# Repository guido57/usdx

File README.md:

This software is derived from https://github.com/threeme3/usdx but it has been completely rewritten for ESP32-S3 N16R8 Devkit C1.

Its hardware is here https://hackaday.io/project/205224-esp32-hf-qrp-ft8-transceiver

# ESP32 SDR Receiver / FT8 Transceiver

This project implements a full **IQ SDR receiver** and **FT8 transceiver** on an ESP32 using external RF front-end circuitry. It includes DSP processing, **FT8 embedded coding and decoding**, audio output via I2S, network audio streaming, and automatic antenna band filtering.  

---

## Features

- True IQ SDR processing: **LSB/USB/AM/CW demodulation**
- High-quality ADC interface: **PCM1808**
- CIC decimation and DC removal
- IQ amplitude/phase calibration
- Selectable audio filters and **AGC**
- Volume control and RIT support
- **Network audio streaming** (websocket) over Wi-Fi or Ethernet
- **Web Server** for remote operations over Wi-Fi or Ethernet
- Automatic **antenna filter selection** via MCP23017 GPIO
- **FT8 TX and RX support** with frequency optimization
- **FT8 embedded coding and decoding** using my library https://github.com/guido57/ESP32_ft8_lib

---

## Architecture Overview

### 1️⃣ RF Front-End
- Tayloe / QSD detector for I/Q extraction
- Connected to **PCM1808 ADC** via I2S
- Optional analog pre-filtering per HF band

### 2️⃣ DSP / Demodulator Pipeline
PCM1808 ADC → CIC Decimator → DC Removal → IQ Calibration → Demodulator → Audio Filter → AGC → Volume → I2S / Wi-Fi

- **CIC Decimation:** 32 kHz → 8 kHz audio
- **IQ Calibration:** corrects phase and amplitude imbalance
- **Demodulator:** supports LSB, USB, AM, CW
- **Audio Filter:** selectable bandwidth for each mode
- **AGC:** peak limiting, attack/release control
- **Audio Output:** I2S DAC (MAX98357) or Wi-Fi streaming

### 3️⃣ RF Control

- **SI5351 driver** for local oscillator generation
- UI-controlled frequency, mode, and filter selection
- Automatic antenna filter switching via MCP23017
- **Filter selection rules:**
  - `< 4 MHz` → 1.8 / 3.5 MHz
  - `< 10 MHz` → 5 / 7 MHz
  - `< 30 MHz` → 14 / 21 / 28 MHz
  - `> 30 MHz` → bypass all

### 4️⃣ FT8 Subsystem

- Integrated **FT8 TX engine**
- Frequency optimization to avoid interferences
- For FT8 decoding, it continuosly streams audio to an external server where a python program:
  - receives audio
  - every 15 seconds runs a command line FT8 decoder (the same used by WSJT-X) to obtain the decoded messages
  - sends back decoded messages to the ESP32

### 5️⃣ Main Loop Execution

```text
loop():
 ├── ui_loop()                (UI interaction)
 ├── processAudioPCM1808()    (DSP pipeline)
 ├── SI5351 update if needed
 ├── antenna filter update
 ├── TX bias control
 └── periodic FT8 frequency optimization
```

### 6️⃣ Hardware Requirements

- ESP32 (any ESP32 variant with enough flash should work). I used ESP32-S3 N16R8 i.e. 16MB Flash, 8MB PSRAM
- PCM1808 ADC
- MAX98357 DAC (I2S audio)
- SI5351 frequency synthesizer
- MCP23017 for antenna relay switching
- Tayloe / QSD or other IQ front-end
- W5500 (optional) for Ethernet

### 7️⃣ Performance Notes

- Designed for efficient CPU usage on ESP32
- DSP pipeline supports real-time audio at 8 kHz
- Wi-Fi streaming allows network SDR operation
- Built-in calibration tools for IQ imbalance and clipping detection

### 8️⃣ ESP32-N16R8 memory partitioning
I adopted a custom partitioning as you can see in my  mypartitions.csv

```text
 Name,   Type, SubType, Offset,   Size, Flags
nvs,      data, nvs,      0x9000,   0x5000,
otadata,  data, ota,      0xe000,   0x2000,
app0,     app,  ota_0,    0x10000,  0x300000,   
app1,     app,  ota_1,    0x310000, 0x300000,   
logs,     data, spiffs,   0x610000, 0x200000,   
spiffs,   data, spiffs,   0x810000, 0x200000,   
coredump, data, coredump, 0xA10000, 0x20000,
```

I halved "data" into "logs" and "spiffs", both with a length of 0x200000 bytes:
- logs is read/written by the program (see qsostats.cpp) to persist QSO scoring but **it is not overwritten when I run 'pio run --target uploadfs'**
- spiffs contains all the files for the web server (index.html, app.js and so on), it is written with all the files contained in /data using 'pio run --target uploadfs' and it is read (only) by the program   

## Web User Interface

- answer a CQ double clicking a row
- follow the evolution of your or other QSOs 
- make a CQ or any other manual FT8 message
- set or disable the automatic frequency offset
- change the FT8 band (160, 80, 60, 40, 30, 20, 15, 10 meters)

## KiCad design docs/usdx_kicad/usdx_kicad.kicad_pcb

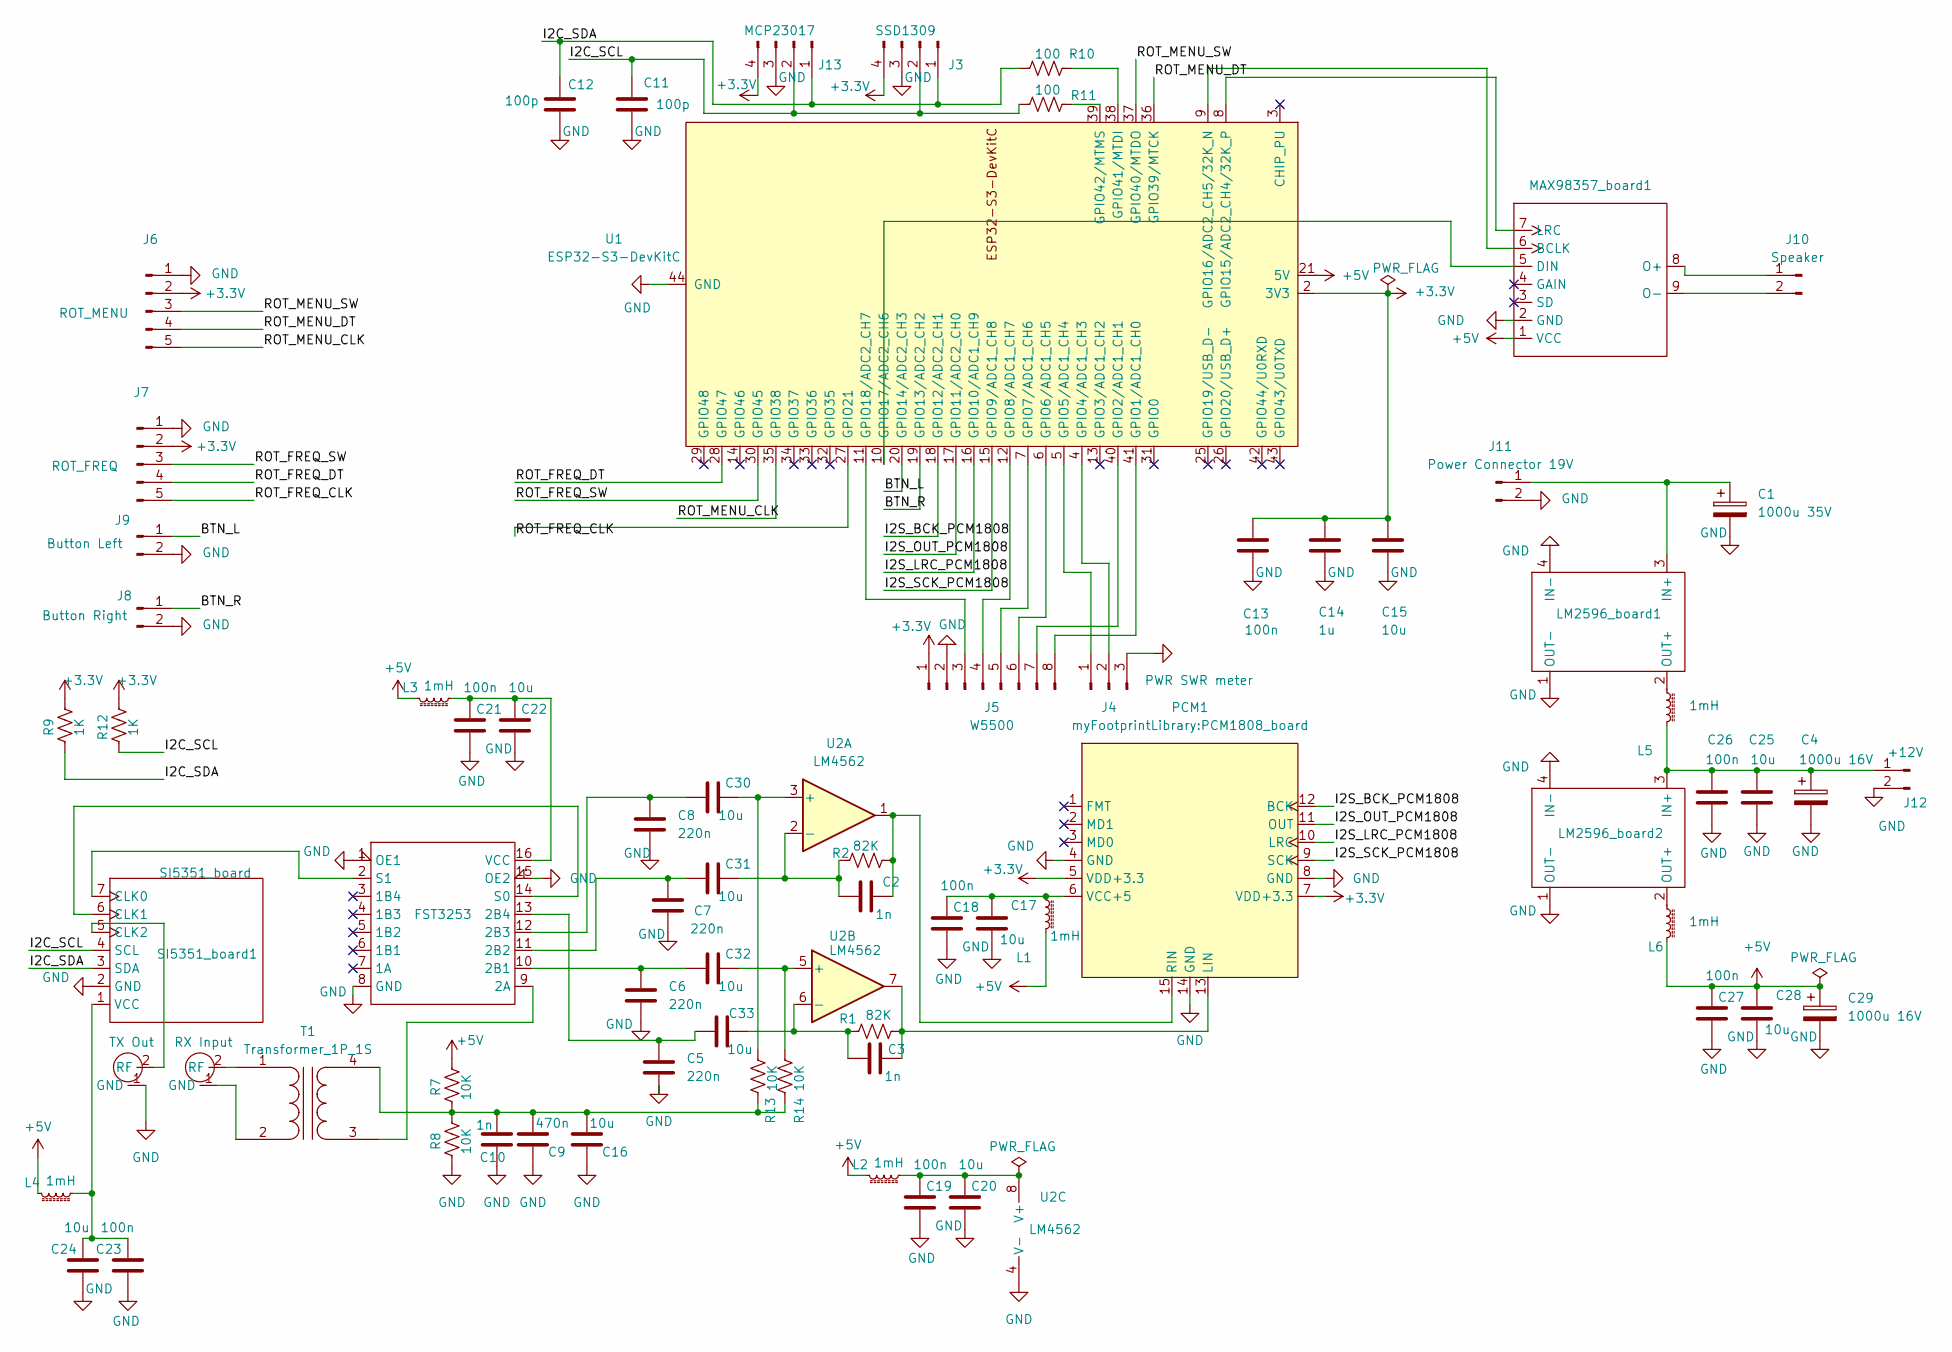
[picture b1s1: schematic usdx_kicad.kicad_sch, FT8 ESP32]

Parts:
C1: 1000u 35V; CP_Radial_D10.0mm_P5.00mm
C2, C3, C10: 1n; C_Disc_D5.0mm_W2.5mm_P5.00mm
C4, C29: 1000u 16V; CP_Radial_D10.0mm_P5.00mm
C5, C6, C7, C8: 220n; C_Rect_L11.5mm_W5.0mm_P10.00mm_MKT
C9: 470n; C_Disc_D5.0mm_W2.5mm_P5.00mm
C11, C12: 100p; C_Disc_D5.0mm_W2.5mm_P5.00mm
C13, C18, C19, C21, C23, C26, C27: 100n; C_Disc_D5.0mm_W2.5mm_P5.00mm
C14: 1u; C_Disc_D5.0mm_W2.5mm_P5.00mm
C15, C16, C17, C20, C22, C24, C25, C28, C30, C31, C32, C33: 10u; C_Disc_D5.0mm_W2.5mm_P5.00mm
FST3253: FST3253_board
J3: SSD1309; PinHeader_1x04_P2.54mm_Vertical
J4: PWR SWR meter; PinHeader_1x03_P2.54mm_Vertical
J5: W5500; PinHeader_1x08_P2.54mm_Vertical
J6: ROT_MENU; PinHeader_1x05_P2.54mm_Vertical
J7: ROT_FREQ; PinHeader_1x05_P2.54mm_Vertical
J8: Button Right; PinHeader_1x02_P2.54mm_Vertical
J9: Button Left; PinHeader_1x02_P2.54mm_Vertical
J10: Speaker; PinHeader_1x02_P2.54mm_Vertical
J11: Power Connector 19V; JST_XH_B2B-XH-A_1x02_P2.50mm_Vertical
J12: +12V; JST_XH_B2B-XH-A_1x02_P2.50mm_Vertical
J13: MCP23017; PinHeader_1x04_P2.54mm_Vertical
L1, L2, L3, L4, L5, L6: 1mH; choke
LM2596_board1, LM2596_board2: LM2596_board
MAX98357_board1: MAX98357_board
PCM1: PCM1808_board
R1, R2: 82K; R_Axial_DIN0207_L6.3mm_D2.5mm_P7.62mm_Horizontal
R7, R8, R13, R14: 10K; R_Axial_DIN0207_L6.3mm_D2.5mm_P7.62mm_Horizontal
R9, R12: 1K; R_Axial_DIN0207_L6.3mm_D2.5mm_P7.62mm_Horizontal
R10, R11: 100; R_Axial_DIN0207_L6.3mm_D2.5mm_P7.62mm_Horizontal
SI5351_board1: SI5351_board
T1: Transformer_1P_1S; transformer
U1: ESP32-S3-DevKitC; ESP32-S3-DevKitC-Mine
U2: LM4562; DIP-8_W7.62mm
U3: RX Input; SMA connector
U4: TX Out; SMA connector

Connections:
+3.3V: C13.1, C14.1, C15.1, J3.4, J5.1, J6.2, J7.2, J13.4, PCM1.5 (VDD+3.3), PCM1.7 (VDD+3.3), R9.2, R12.2, U1.1 (3V3), U1.2 (3V3)
+5V: C27.1, C28.1, C29.1, L1.2, L2.2, L3.2, L4.2, L6.2, MAX98357_board1.1 (VCC), R7.2, U1.21 (5V)
/BTN_L: J9.1, U1.20 (GPIO14/ADC2_CH3)
/BTN_R: J8.1, U1.19 (GPIO13/ADC2_CH2)
/I2C_SCL: C11.1, J3.2, J13.2, R11.2, R12.1, SI5351_board1.4 (SCL)
/I2C_SDA: C12.1, J3.1, J13.1, R9.1, R10.2, SI5351_board1.3 (SDA)
/I2S_BCK_PCM1808: PCM1.12 (BCK), U1.18 (GPIO12/ADC2_CH1)
/I2S_LRC_PCM1808: PCM1.10 (LRC), U1.16 (GPIO10/ADC1_CH9)
/I2S_OUT_PCM1808: PCM1.11 (OUT), U1.17 (GPIO11/ADC2_CH0)
/I2S_SCK_PCM1808: PCM1.9 (SCK), U1.15 (GPIO9/ADC1_CH8)
/ROT_FREQ_CLK: J7.5, U1.27 (GPIO21)
/ROT_FREQ_DT: J7.4, U1.28 (GPIO47)
/ROT_FREQ_SW: J7.3, U1.30 (GPIO45)
/ROT_MENU_CLK: J6.5, U1.35 (GPIO38)
/ROT_MENU_DT: J6.4, U1.36 (GPIO39/MTCK)
/ROT_MENU_SW: J6.3, U1.37 (GPIO40/MTDO)
GND: C1.2, C4.2, C5.2, C6.2, C7.2, C8.2, C9.2, C10.2, C11.2, C12.2, C13.2, C14.2, C15.2, C16.2, C17.2, C18.2, C19.2, C20.2, C21.2, C22.2, C23.2, C24.2, C25.2, C26.2, C27.2, C28.2, C29.2, FST3253.1 (OE1), FST3253.8 (GND), FST3253.15 (OE2), J3.3, J4.3, J5.2, J6.1, J7.1, J8.2, J9.2, J11.2, J12.2, J13.3, LM2596_board1.1 (OUT-), LM2596_board1.4 (IN-), LM2596_board2.1 (OUT-), LM2596_board2.4 (IN-), MAX98357_board1.2 (GND), PCM1.4 (GND), PCM1.8 (GND), PCM1.14 (GND), R8.1, SI5351_board1.2 (GND), U1.22 (GND), U1.23 (GND), U1.24 (GND), U1.44 (GND), U2.4 (V-), U4.1 (GND)
unnamed: FST3253.9 (2A), T1.3 (SA)
unnamed: C6.1, C32.2, FST3253.10 (2B1)
unnamed: C7.1, C31.2, FST3253.11 (2B2)
unnamed: C8.1, C30.2, FST3253.12 (2B3)
unnamed: C5.1, C33.2, FST3253.13 (2B4)
unnamed: FST3253.14 (S0), SI5351_board1.6 (CLK1)
unnamed: FST3253.2 (S1), SI5351_board1.7 (CLK0)
unnamed: C21.1, C22.1, FST3253.16 (VCC), L3.1
unnamed: J4.1, U1.5 (GPIO5/ADC1_CH4)
unnamed: J4.2, U1.4 (GPIO4/ADC1_CH3)
unnamed: J5.3, U1.11 (GPIO18/ADC2_CH7)
unnamed: J5.4, U1.12 (GPIO8/ADC1_CH7)
unnamed: J5.5, U1.7 (GPIO7/ADC1_CH6)
unnamed: J5.6, U1.6 (GPIO6/ADC1_CH5)
unnamed: J5.7, U1.40 (GPIO2/ADC1_CH1)
unnamed: J5.8, U1.41 (GPIO1/ADC1_CH0)
unnamed: J10.1, MAX98357_board1.8 (O+)
unnamed: J10.2, MAX98357_board1.9 (O-)
unnamed: C1.1, J11.1, LM2596_board1.3 (IN+)
unnamed: C4.1, C25.1, C26.1, J12.1, L5.2, LM2596_board2.3 (IN+)
unnamed: L5.1, LM2596_board1.2 (OUT+)
unnamed: L6.1, LM2596_board2.2 (OUT+)
unnamed: MAX98357_board1.6 (BCLK), U1.9 (GPIO16/ADC2_CH5/32K_N)
unnamed: MAX98357_board1.5 (DIN), U1.10 (GPIO17/ADC2_CH6)
unnamed: MAX98357_board1.7 (LRC), U1.8 (GPIO15/ADC2_CH4/32K_P)
unnamed: C3.1, PCM1.13 (LIN), R1.1, U2.7
unnamed: C2.1, PCM1.15 (RIN), R2.1, U2.1
unnamed: C17.1, C18.1, L1.1, PCM1.6 (VCC+5)
unnamed: SI5351_board1.5 (CLK2), U4.2 (RF)
unnamed: C23.1, C24.1, L4.1, SI5351_board1.1 (VCC)
unnamed: T1.1 (AA), U3.2 (RF)
unnamed: T1.2 (AB), U3.1 (GND)
unnamed: C9.1, C10.1, C16.1, R7.1, R8.2, R13.1, R14.1, T1.4 (SB)
unnamed: R10.1, U1.38 (GPIO41/MTDI)
unnamed: R11.1, U1.39 (GPIO42/MTMS)
unnamed: C30.1, R13.2, U2.3 (+)
unnamed: C2.2, C31.1, R2.2, U2.2 (-)
unnamed: C32.1, R14.2, U2.5 (+)
unnamed: C3.2, C33.1, R1.2, U2.6 (-)
unnamed: C19.1, C20.1, L2.1, U2.8 (V+)

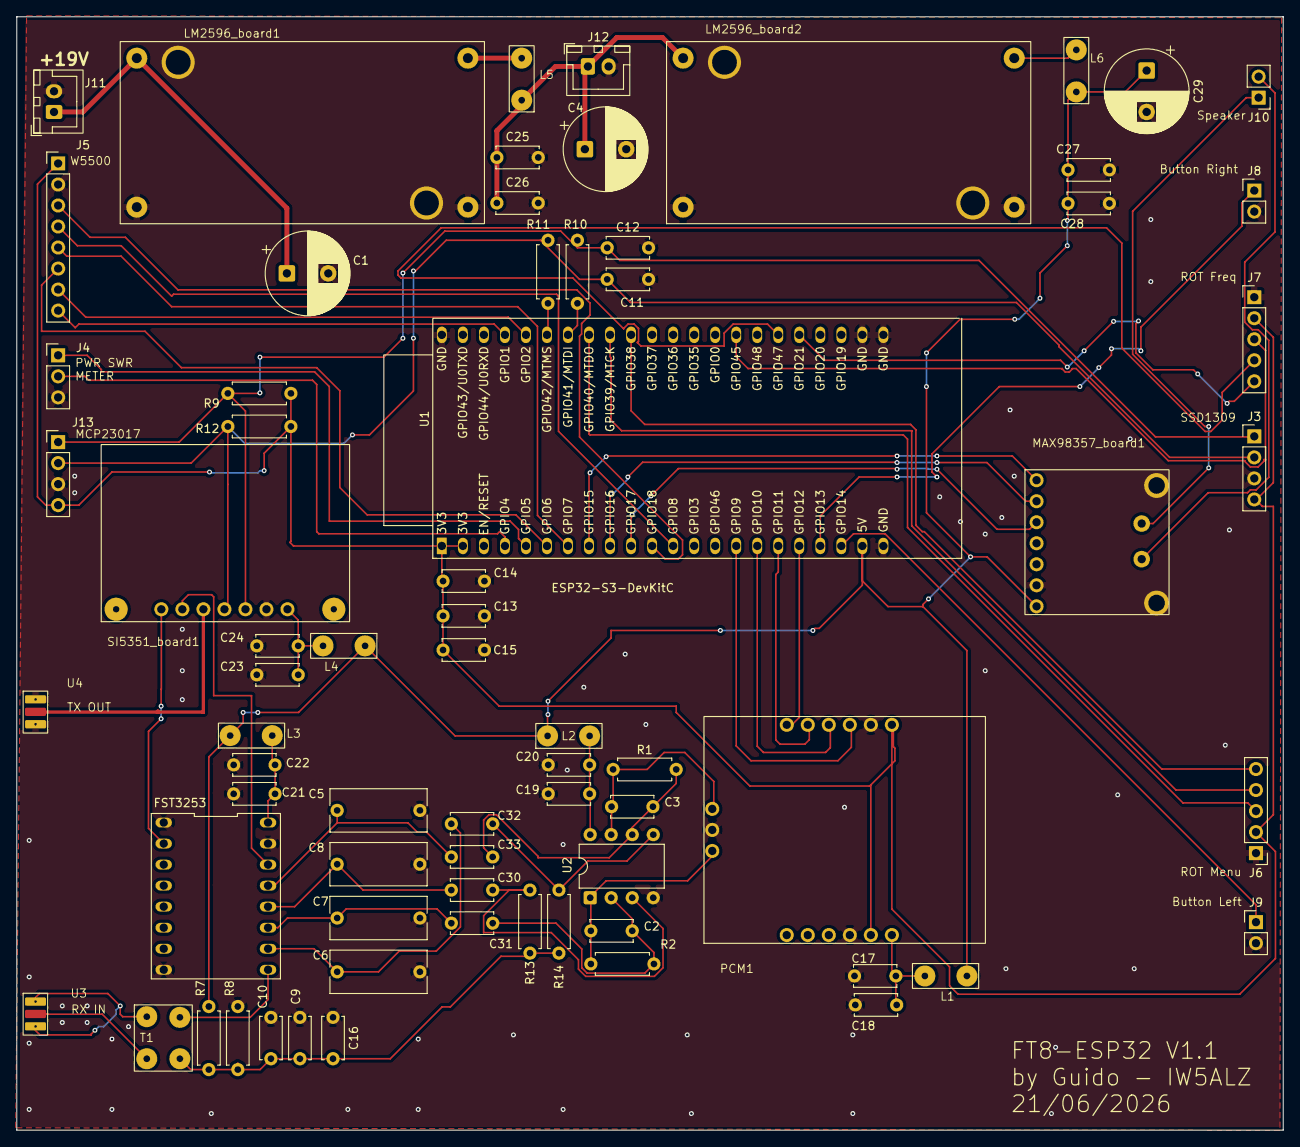
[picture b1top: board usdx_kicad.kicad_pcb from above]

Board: 2 copper layers, 153.0 x 134.5 mm, 71 parts (0 on the bottom side), 57 nets.

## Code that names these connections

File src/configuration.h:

#pragma once

#define VERSION   "0.01"

// rotary encoder_freq frequency and step size
#define GPIO_ROT_A     47  // GPIO pin for rotary encoder_freq A
#define GPIO_ROT_B     21  // GPIO pin for rotary encoder_freq B   
#define GPIO_ROT_SW    45  // GPIO pin for rotary encoder_freq switch  
#define GPIO_L_SW      13  // GPIO pin for left pushbutton switch   
#define GPIO_R_SW      14  // GPIO pin for right pushbutton switch

// rotary encoder menu parameters
#define GPIO_ROT_MENU_A   39 // GPIO pin for menu rotary encoder A
#define GPIO_ROT_MENU_B   38 // GPIO pin for menu rotary encoder B 
#define GPIO_ROT_MENU_SW  40 // GPIO pin for menu rotary encoder switch

// I2C pins (shared bus for all devices)
#define I2C_SDA 41
#define I2C_SCL 42

// SI5351 configuration (used by src/phy/si5351.h)
#ifndef F_XTAL
#define F_XTAL 25000000UL
#endif

#ifndef SI5351_ADDR
#define SI5351_ADDR 0x60
#endif

#ifndef ANT_FILTERS_ADDR
#define ANT_FILTERS_ADDR 0x21   // A0=1 A1=0 A2=0
#endif	

#define CLK2

// Set to 1 to print SI5351 programming details over Serial.
#ifndef SYNTH_DEBUG
#define SYNTH_DEBUG 0
#endif

// Default test wiring for ESP32-S3 DevKitC: use GPIO5/GPIO5 (ADC-capable and typically exposed).
// Some modules/board variants reserve GPIO9/10 for flash signals; IDF may reject them.
#define GPIO_ADC_I 6
#define GPIO_ADC_Q 7

// -------------------- PCM1808 ADC Pin mapping --------------------
#define I2S_BCK_PCM1808   12
#define I2S_DIN_PCM1808   11
#define I2S_WS_PCM1808    10
#define I2S_MCLK_PCM1808   9

#define GPIO_PWM_RX_ATT  5  // PWM output for ATT control
#define GPIO_PWM_TX_BIAS 4  // PWM output for biasing power amplifier

#define GPIO_TX         18  // Switch the relay to TX mode. High=TX Low=RX

#define QSO_LIST_MAX 100 // Maximum number of QSOs to track in memory


// IQ ADC sampling configuration (ESP32)
// main.ori uses a 62.5kHz timer ISR and alternates I/Q each tick, i.e. ~31.25kS/s per channel.

// This project uses the ESP-IDF ADC continuous driver for I/Q sampling.
// If you ever need a non-IDF fallback again, reintroduce a feature flag and
// implement a separate ADC backend.
#if !defined(ARDUINO_ARCH_ESP32)
	#error "IQ ADC requires ESP32 + ESP-IDF ADC continuous driver"
#endif

#ifndef IQ_ADC_CONV_RATE_HZ
	#define IQ_ADC_CONV_RATE_HZ 64000U
#endif

// DC removal ("DC decoupling") for raw I/Q samples.
// Implemented as a slow running average (IIR) in fixed-point:
//   dcQ8 += ((x<<8) - dcQ8) >> IQ_ADC_DC_SHIFT;
//   y = x - (dcQ8>>8)
// With IQ_ADC_DC_SHIFT=8 and Fs≈31250S/s per channel, the high-pass cutoff is ~20Hz.
#ifndef IQ_ADC_DC_SHIFT
	#define IQ_ADC_DC_SHIFT 8
#endif

// How many I/Q pairs to buffer in RAM (consumer can pop later).
// 8192 pairs ~= 8192 / 31250 = 0.262s of headroom.
#ifndef IQ_ADC_RING_SIZE
	#define IQ_ADC_RING_SIZE 8192U
#endif

// ADC DMA buffering (continuous mode).
// Data rate is IQ_ADC_CONV_RATE_HZ * 4 bytes/result.
#ifndef IQ_ADC_DMA_MAX_STORE_BYTES
	#define IQ_ADC_DMA_MAX_STORE_BYTES 65536U
#endif

#ifndef IQ_ADC_DMA_FRAME_BYTES
	#define IQ_ADC_DMA_FRAME_BYTES 2048U
#endif

// Background ADC reader task tuning.
#ifndef IQ_ADC_TASK_PRIORITY
	#define IQ_ADC_TASK_PRIORITY 20
#endif

#ifndef IQ_ADC_TASK_STACK
	#define IQ_ADC_TASK_STACK 4096
#endif

#ifndef IQ_ADC_TASK_CORE
	// -1 = let scheduler choose; 0/1 pins the task to a core.
	#define IQ_ADC_TASK_CORE -1
#endif

// Set to 1 to print ADC noise stats every 5 seconds.
#ifndef IQ_ADC_NOISE_LOG
  #define IQ_ADC_NOISE_LOG 0
#endif

// Set to 1 to enable image rejection / IQ debug logs in main loop.
#ifndef IQ_MEASURE_LOG
	#define IQ_MEASURE_LOG 1
#endif

// Set to 0 to disable AGC processing entirely.
#ifndef ENABLE_AGC
	#define ENABLE_AGC 1
#endif

// AM AGC tuning (applied after demod + filter)
#ifndef AM_AGC_TARGET
	#define AM_AGC_TARGET 12000.0f
#endif
#ifndef AM_AGC_MAX_GAIN
	#define AM_AGC_MAX_GAIN 8.0f
#endif
#ifndef AM_AGC_MIN_GAIN
	#define AM_AGC_MIN_GAIN 0.1f
#endif
#ifndef AM_AGC_ATTACK
	#define AM_AGC_ATTACK 0.02f
#endif
#ifndef AM_AGC_DECAY
	#define AM_AGC_DECAY 0.0015f
#endif

// AM demodulation mode: 1 = coherent (I only), 0 = envelope magnitude
#ifndef AM_DEMOD_COHERENT
	#define AM_DEMOD_COHERENT 0
#endif

// AM demod test mode (internal IQ generator)
#ifndef AM_TEST_MODE
	#define AM_TEST_MODE 0
#endif
#ifndef AM_TEST_CARRIER_HZ
	#define AM_TEST_CARRIER_HZ 1000.0f
#endif
#ifndef AM_TEST_MOD_HZ
	#define AM_TEST_MOD_HZ 500.0f
#endif
#ifndef AM_TEST_DEPTH
	#define AM_TEST_DEPTH 0.0f
#endif
#ifndef AM_TEST_AMPLITUDE
	#define AM_TEST_AMPLITUDE 12000.0f
#endif

// I2S Audio Output (MAX98357 amplifier)
// GPIO pins for I2S (MAX98357)
#define GPIO_I2S_LRC   15  // Left/Right clock (word select)
#define GPIO_I2S_BCLK  16  // Bit clock
#define GPIO_I2S_DOUT  17  // Data out

// Audio sample rate (8kHz for 4kHz bandwidth)
#define AUDIO_I2S_SAMPLE_RATE 8000

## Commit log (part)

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2026-01-05 Initial plan
2026-01-05 Add comprehensive IQ mux/demux documentation
2026-01-10 Convert to PlatformIO project with ESP32-S3 support
    - Migrate from Arduino IDE to PlatformIO
    - Add ESP32-S3 with PSRAM support
    - Implement I2S audio output using legacy driver (PSRAM compatible)
    - Add IQ ADC sampling with continuous driver
    - Add CIC decimating filter for DSP
    - Add demodulation modes (LSB/USB/AM/FM/CW)
2026-01-18 Add waterfall and IQ timing calibration
2026-01-26 bidirectiona websocket
2026-01-26 new 50 - 2900 Hz
2026-01-26 fixed delay
2026-01-26 minor
2026-01-26 AM_DEMOD_COEHERENT added
2026-01-26 AM improved
2026-03-13 PCM1808 version
2026-03-13 Simplify README by removing detailed project information
    Removed extensive project description and features list to streamline README.
2026-03-13 Enhance README with project overview and features
    Expanded README with detailed project features, architecture, and hardware requirements.
2026-03-13 Update README with hardware project link
    Added hardware project link for ESP32 HF QRP FT8 transceiver.
2026-03-13 Update section titles in README.md with emojis
2026-03-13 Add hardware requirements section to README
2026-03-13 Remove extra line in RF Front-End section
2026-04-13 Update FT8 TX, UI, and web assets
2026-04-21 distance and flags added
2026-04-21 QSO_LIST_MAX added
2026-04-21 frequency optimizator added
2026-04-21 freq optimizator added
2026-04-21 minor changes
2026-04-27 Update hardware requirements and section numbering
2026-04-27 Clarify logs and spiffs sections in README
    Updated the README to clarify the purpose of 'logs' and 'spiffs' sections.
2026-04-27 Update README to clarify logs and spiffs usage
2026-04-27 Update README with architecture overview
    Add architecture overview image and details for RF front-end.
2026-04-27 Fix image syntax in README.md
2026-04-27 Revise ESP32-N16R8 memory partitioning section
    Updated memory partitioning details in README.md to clarify the structure and purpose of 'logs' and 'spiffs'.
2026-05-15 Replace architecture image in README
    Updated architecture overview image in README.
2026-05-15 Clarify network audio streaming and add web server info
    Updated README to clarify network audio streaming and added web server details.
2026-05-15 Fix formatting of 'Web Server' in README.md
2026-05-15 Enhance README with FT8 decoding and UI info
    Added details about FT8 decoding process and web user interface.
2026-05-15 Update README with new UI features
    Added features to the Web User Interface section.
2026-05-17 Update FT8, UI, WiFi, and data files with latest changes
2026-05-17 Integrate FT8 decoder as git submodule with PlatformIO configuration
2026-05-17 Fix FT8 decoder build: use pre-script BuildSources, exclude duplicate src/ft8/ files
2026-05-19 MAX_CANDIDATES added
2026-05-19 deleted
2026-05-19 moved
2026-05-20 feat: Convert WebSocket client to server mode
    - Replace WebSocketsClient with WebSocketsServer
    - Remove client-side reconnect/backoff logic
    - Update event handler for server-mode events (num parameter)
    - Replace send operations with broadcast methods
    - Use ui_get_ws_server_port() for dynamic port configuration
    - Update both NetworkTask (Ethernet) and WiFiNetworkTask
2026-05-21 Fix streaming: buffer, task priority, polling, and FT8 integration updates
2026-05-21 Remove embedded .history gitlink and ignore KiCad history folder
2026-05-25 Add KiCad PCB build files and ignore local artifacts
2026-05-25 typo corrected
2026-05-25 Fix FT8 parseMessage null dereference on empty payload
2026-05-26 my Rig implemented
2026-05-26 som cleaning
2026-05-29 Audio bufferiing reduced
2026-05-29 Audio buffering improved
2026-05-29 FT8 internal decoder
2026-05-29 typo
2026-05-29 audio level reduced
2026-05-30 warning
2026-05-30 enhanced log
2026-05-30 clean
2026-05-31 taskprofiler
2026-06-01 measure tasks added
2026-06-07 ft8 autocall
2026-06-07 allQSO straming
2026-06-07 ft8 autocall added
2026-06-07 Enhance README with FT8 coding and decoding details
    Added FT8 embedded coding and decoding to project description.
2026-06-07 Fix link formatting for FT8 library in README
2026-06-13 small mistake
2026-06-13 guard on fetch
2026-06-13 less verbose
2026-06-13 little mistake
2026-06-14 new class to stream audio in a sepatate task
2026-06-20 comments
2026-06-20 favicon
2026-06-20 drive_strength introduced
2026-06-20 IQ balance introduced
2026-06-20 prova
2026-06-21 LM4562 DC decoupling
2026-06-25 PCB version 1.1
2026-06-25 works without MCP23017
2026-06-25 I2C at 100KHz
2026-06-25 No option < 3.5MHz
2026-06-25 cleaning
2026-06-25 debug
2026-06-28 new RGB LED diagnostics
2026-06-28 smaller
2026-06-28 capacitors voltage
2026-06-28 runtime error solved
2026-06-29 set \r\n in all printf
